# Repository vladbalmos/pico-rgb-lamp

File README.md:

# RGB Lamp based on RP2040

An RGB lamp powered by a Raspberry Pi Pico, offering seamless control via MQTT. Customize your lighting experience with simple commands for color changes, dynamic animations, and an audio visualizer mode.

### Features:
- **MQTT Control**
- **Color Selection**
- **Animation Selection**
- **Audio Visualizer Mode**: Requires [python-fft-streamer](https://github.com/vladbalmos/python-fft-streamer).

This project is part of my basic home automation suit and requires the [pihub](https://github.com/vladbalmos/pihub) server for remote control.

#### Demo

[View on YouTube](https://www.youtube.com/watch?v=2PfCFWdMnYo)

# System requirements

* micropython (RPI_PICO_W-20240602-v1.23.0)
* mpremote

For a complete bill of materials see the [hw/pcb](https://github.com/vladbalmos/pico-rgb-lamp/tree/main/hw/pcb/rgb-lamp) folder.

# Install

    git clone https://github.com/vladbalmos/pico-rgb-lamp
    git submodule update --init --recursive
    
# Building and flashing
Copy `device.tpl.json` to `device.json` and configure your wifi & mqtt settings. See [Device configuration](#device-configuration) for available options

## Linux

## Windows

    build.ps1 -Command build
    
# Runnig while in development

Once micropython is flashed and the source code files are copied to the device (see [Building and flashing](#building-and-flashing)) run:

    build.ps1 -Command run
    
This will reset the device first, copy the `src/` dir to the device and then call `mpremote run src/main.py`

# Device configuration

The configuration is provided in JSON format and is used to customize various aspects of the lamp, including its MQTT communication, features, and hardware setup.

## Configuration Fields

### 1. `id`
- **Type**: String
- **Description**: A unique identifier for the RGB MQTT Lamp.
- **Example**: `"RGB_MQTT_LAMP_001"`

### 2. `name`
- **Type**: String
- **Description**: The name of the RGB MQTT Lamp.
- **Example**: `"RGB MQTT Lamp"`

### 3. `ssid`
- **Type**: String
- **Description**: The SSID of the WiFi network to which the lamp should connect.

### 4. `password`
- **Type**: String
- **Description**: The password for the WiFi network.

### 5. `server`
- **Type**: String
- **Description**: The IP address or domain of the MQTT server that the lamp will communicate with.
- **Example**: `"mqtt.example.com"`

### 6. `config`
- **Type**: Object
- **Description**: Configuration related to the hardware setup and features of the lamp.

#### 6.1 `led_pins`
- **Type**: Array of integers
- **Description**: The GPIO pins used for controlling the RGB channels: [red pin, green pin, blue pin]
- **Example**: `[0, 1, 2]`

#### 6.2 `rotary_encoder_pins`
- **Type**: Array of integers
- **Description**: The GPIO pins used for the rotary encoder: [clk_pin, dt_pin]
- **Example**: `[14, 13]`

#### 6.3 `select_switch_pin`
- **Type**: Integer
- **Description**: The GPIO pin used for the select switch.
- **Example**: `15`

#### 6.4 `invert_pwm_duty_cycle`
- **Type**: Boolean
- **Description**: Whether to invert the PWM duty cycle for LED control. Usefull when using PNP / P-MOSFET drivers
- **Example**: `false`

#### 6.5 `fft_streamer`
- **Type**: Object
- **Description**: Configuration for the FFT (Fast Fourier Transform) streamer used in the audio visualizer. Not required - the lamp will automatically subscribe to the streamer mqtt channel and autoconfigure, see [python-fft-streamer](https://github.com/vladbalmos/python-fft-streamer)

##### `host`
- **Type**: String or null
- **Description**: The host for the FFT streamer.
- **Example**: `null`

##### `port`
- **Type**: Integer or null
- **Description**: The port for the FFT streamer.
- **Example**: `null`

#### 6.6 `available_colors`
- **Type**: Array of strings
- **Description**: A list of predefined colors available for selection. Colors are defined in hexadecimal format.
- **Example**: `["#ffffff", "#ff0000", "#00ff00", "#0000ff", "#ffff00", "#00ffff", "#ff00ff"]`

### 7. `features`
- **Type**: Array of objects
- **Description**: A list of features that the RGB MQTT Lamp supports.

#### 7.1 `name`
- **Type**: String
- **Description**: The name of the feature.
- **Example**: `"Change global color"`

#### 7.2 `id`
- **Type**: String
- **Description**: A unique identifier for the feature.
- **Example**: `"change_global_color"`

#### 7.3 `schema`
- **Type**: Object
- **Description**: The schema that defines the configuration options for the feature.

##### `type`
- **Type**: String
- **Description**: The data type of the feature's configuration value.
- **Example**: `"color"`, `"boolean"`, `"json"`, `"list"`

##### `default`
- **Type**: Depends on `type`
- **Description**: The default value for the feature's configuration.

###### For `change_global_color`:
- **Example**: `"#ff0000"`

###### For `enable_audio_visualizer`:
- **Example**: `false`

###### For `audio_visualizer_config`:
- **Example**: JSON object with audio visualizer settings.

###### For `animation`:
- **Example**: `"off"`

#### 7.4 `valid_values` (for `list` type)
- **Type**: Array of strings
- **Description**: A list of valid values for the feature.
- **Example**: `["off", "breathe", "wheel", "rainbow"]`

### 8. `topics`
- **Type**: Object
- **Description**: The MQTT topics used for subscription and publishing.

#### 8.1 `subscription`
- **Type**: Object
- **Description**: MQTT topics to which the lamp subscribes.

##### `manager`
- **Type**: String
- **Description**: The MQTT topic for manager requests.
- **Example**: `"acme/devices/request"`

##### `lighting`
- **Type**: String
- **Description**: The MQTT topic for lighting control.
- **Example**: `"acme/devices/lighting"`

##### `device`
- **Type**: String
- **Description**: The MQTT topic for device-specific requests.
- **Example**: `"acme/devices/lighting/name-of-device/request"`

#### 8.2 `publish`
- **Type**: Object
- **Description**: MQTT topics to which the lamp publishes messages.

##### `manager`
- **Type**: String
- **Description**: The MQTT topic for manager responses.
- **Example**: `"acme/devices/response"`

##### `device`
- **Type**: String
- **Description**: The MQTT topic for device-specific responses.
- **Example**: `"acme/devices/lighting/name-of-device/response"`

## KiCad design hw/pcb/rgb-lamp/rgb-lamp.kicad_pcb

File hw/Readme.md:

# Hardware design files

The `bulb-fixture` & `case` folders contains CAD files for a custom light bulb fixture & enclosure specifically design for a lamp I own, I doubt it would be of any use to anyone else. There's some pictures in there if you want to see what's it all about.

The PCB was designed with manual tracing in mind so the tracks are wider than they should be.

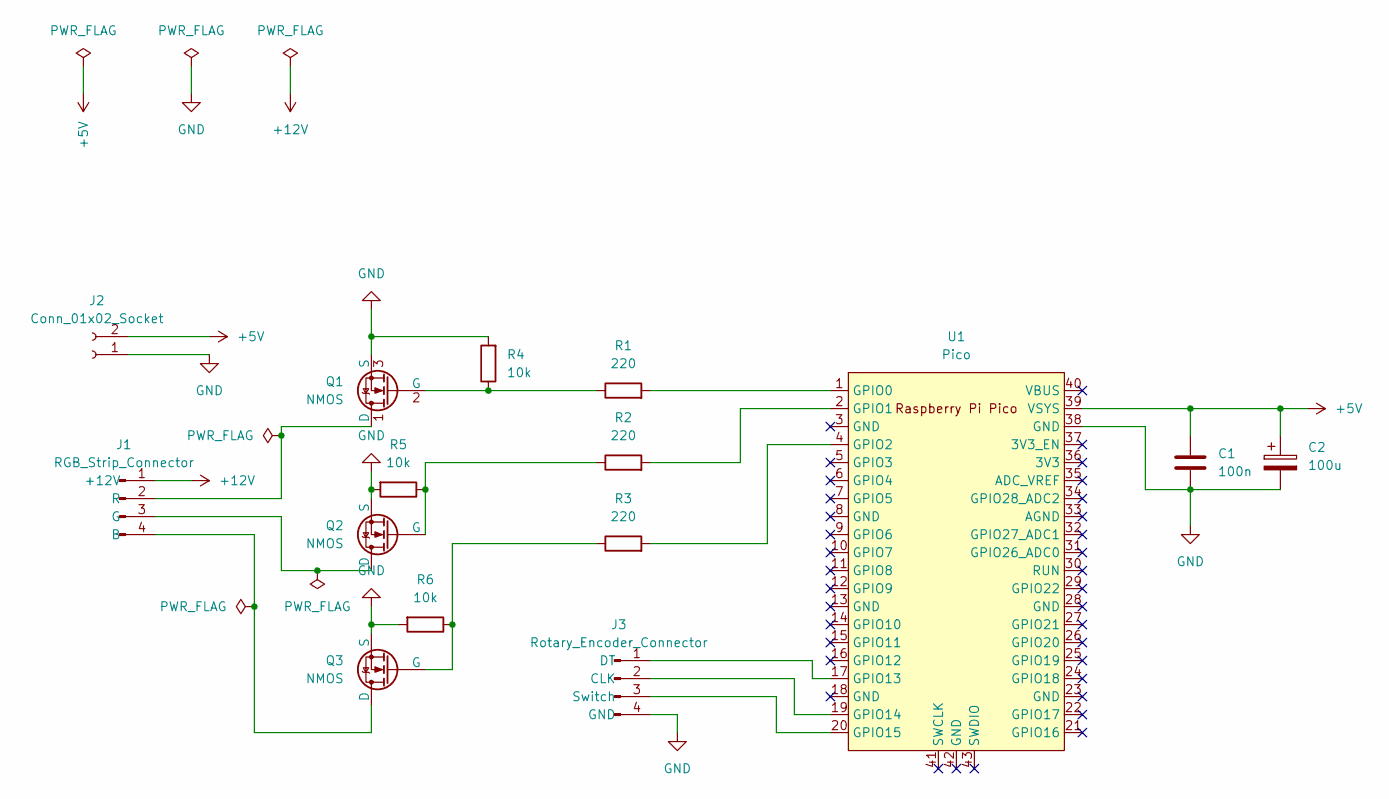
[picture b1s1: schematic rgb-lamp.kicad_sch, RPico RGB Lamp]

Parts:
C1: 100n; C_Disc_D8.0mm_W5.0mm_P5.00mm
C2: 100u; CP_Radial_D5.0mm_P2.50mm
J1: RGB_Strip_Connector; JST_XH_B4B-XH-A_1x04_P2.50mm_Vertical
J2: Conn_01x02_Socket; JST_XH_B2B-XH-A_1x02_P2.50mm_Vertical
J3: Rotary_Encoder_Connector; JST_XH_B4B-XH-A_1x04_P2.50mm_Vertical
Q1, Q2, Q3: NMOS; TO-92_Inline
R1, R2, R3: 220; R_Axial_DIN0207_L6.3mm_D2.5mm_P10.16mm_Horizontal
R4, R5, R6: 10k; R_Axial_DIN0207_L6.3mm_D2.5mm_P10.16mm_Horizontal
U1: Pico; RPi_Pico_SMD_TH

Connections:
+5V: C1.1, C2.1, J2.2, U1.39 (VSYS)
+12V: J1.1 (+12V)
GND: C1.2, C2.2, J2.1, J3.4 (GND), Q1.3 (S), Q2.3 (S), Q3.3 (S), R4.2, R5.2, R6.2, U1.38 (GND)
unnamed: J1.4 (B), Q3.1 (D)
unnamed: J1.3 (G), Q2.1 (D)
unnamed: J1.2 (R), Q1.1 (D)
unnamed: J3.2 (CLK), U1.19 (GPIO14)
unnamed: J3.1 (DT), U1.17 (GPIO13)
unnamed: J3.3 (Switch), U1.20 (GPIO15)
unnamed: Q1.2 (G), R1.1, R4.1
unnamed: Q2.2 (G), R2.1, R5.1
unnamed: Q3.2 (G), R3.1, R6.1
unnamed: R1.2, U1.1 (GPIO0)
unnamed: R2.2, U1.2 (GPIO1)
unnamed: R3.2, U1.4 (GPIO2)

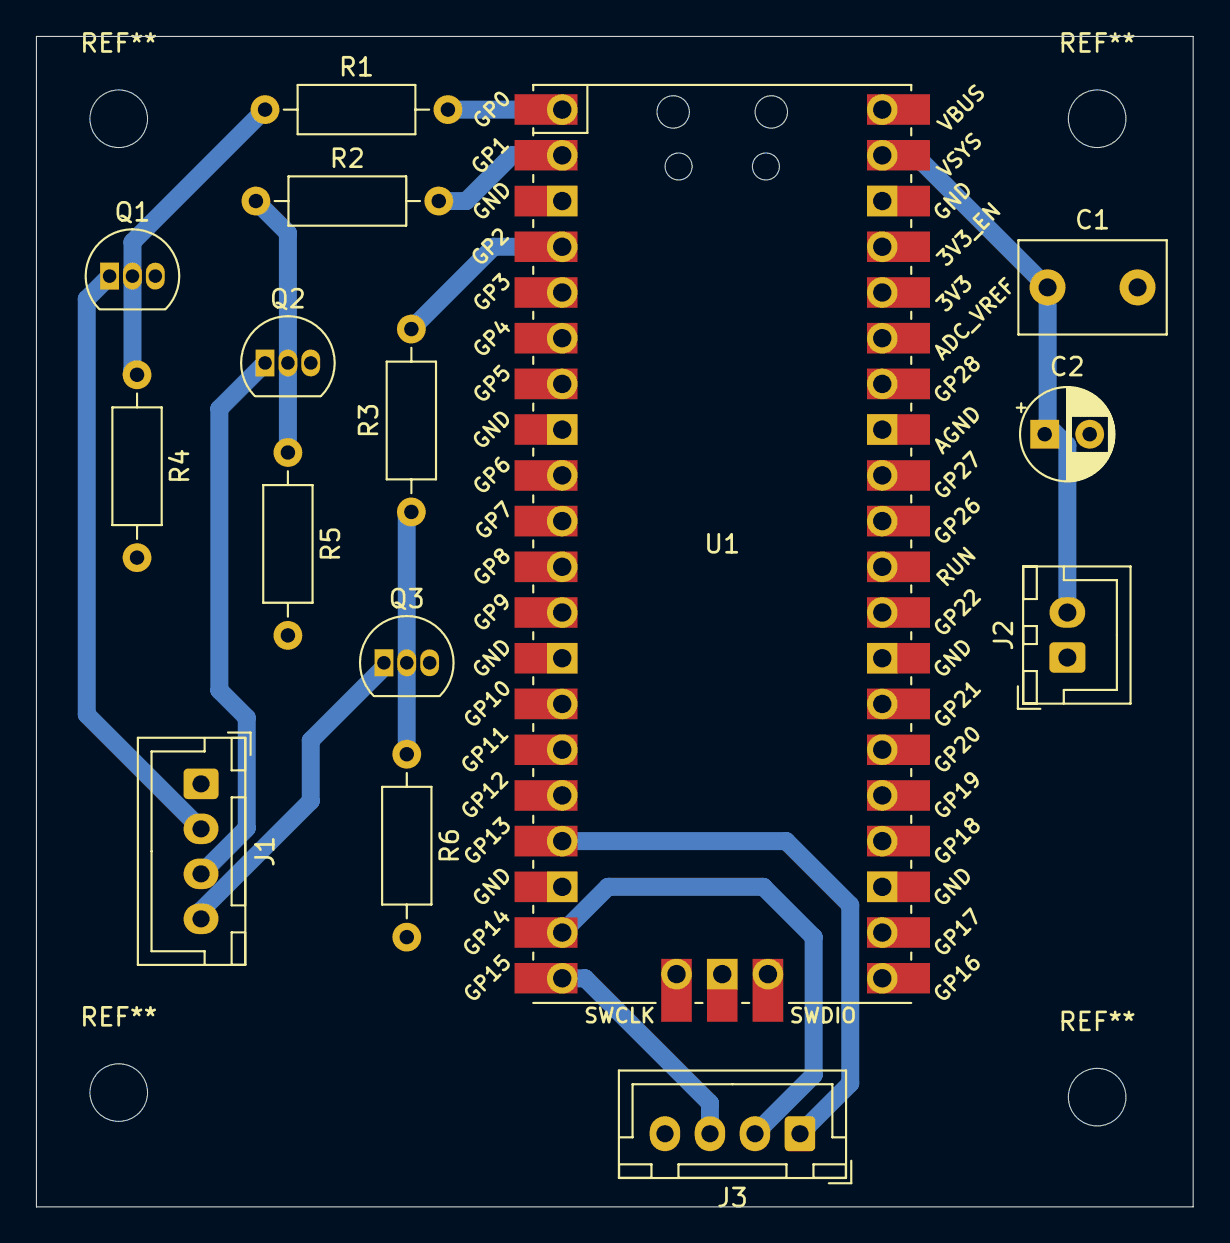
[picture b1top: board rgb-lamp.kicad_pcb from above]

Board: 2 copper layers, 64.3 x 65.0 mm, 15 parts (0 on the bottom side), 14 nets.

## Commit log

2024-07-14 Add micropython asyncio extras
2024-07-14 Work in progress
2024-07-17 Start work on animations
2024-07-18 Remove unwanted file
2024-07-22 Update animation
2024-07-24 Work on processing fft values
2024-08-04 Bug fixes
2024-08-04 Bug fix
2024-08-04 Reconnect if server is down
2024-08-04 Refactor and simplify code
2024-08-05 Add support for audio visualizer mqtt config
2024-08-06 Simplify configuration
2024-08-11 Add rotary encoder lib
2024-08-11 Start work on UI
2024-08-11 Drop global state
2024-08-12 ADd support for UI using rotary encoder and microswitch
2024-08-13 Alpha version finished
2024-08-13 Add schematic and pcb design
2024-08-20 Add more docs
2024-08-20 Fix link
